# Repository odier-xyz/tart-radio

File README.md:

TART-Frontend
-------------

Radio module
------------

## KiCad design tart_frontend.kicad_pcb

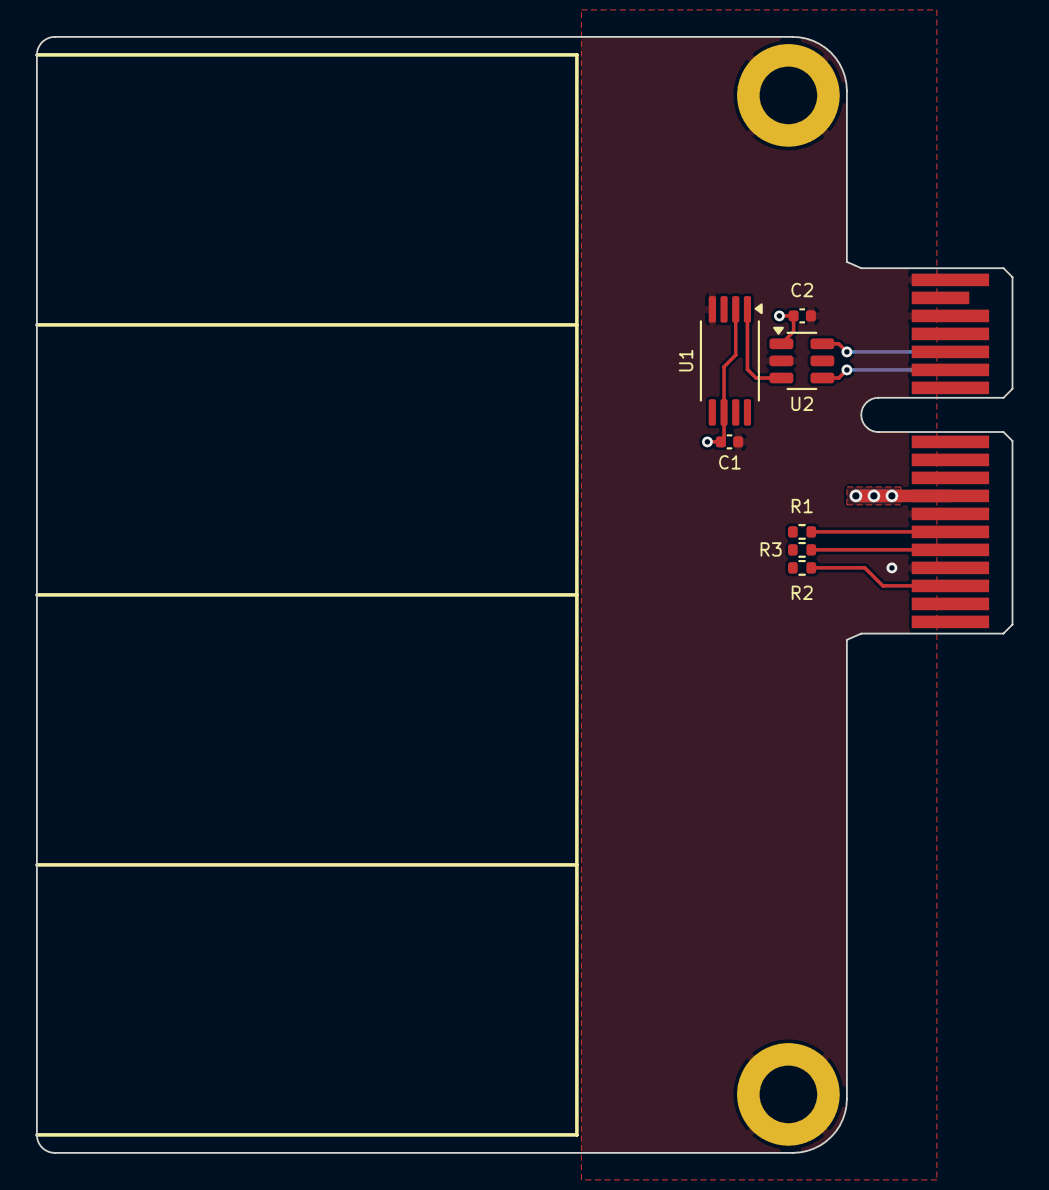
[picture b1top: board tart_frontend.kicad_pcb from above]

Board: 6 copper layers, 54.2 x 62.0 mm, 10 parts (0 on the bottom side), 8 nets.

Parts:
C1, C2: 100n; C_0402_1005Metric
H1, H2: GND; MountingHole_3.2mm_M3_ISO7380_Pad
J1: BUS_PCIexpress_x1
R1, R2, R3: 100; R_0402_1005Metric
U1: CDCV304PW; TSSOP-8_4.4x3mm_P0.65mm
U2: MAX3280E; SOT-23-6

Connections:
GNDREF: C1.1, C2.2, H1.1, H2.1, J1.A4 (GND), J1.A12 (GND), J1.A15 (GND), J1.A18 (GND), J1.B4 (GND), J1.B7 (GND), J1.B13 (GND), J1.B16 (GND), J1.B18 (GND), U1.4 (gnd), U2.2 (GND)
unnamed: J1.A13 (REFCLK+), U2.4 (B)
unnamed: J1.A14 (REFCLK-), U2.6 (A)
unnamed: J1.B6 (SCLK), R1.1
unnamed: J1.B3 (SDATA), R2.1
unnamed: J1.B5 (~CS), R3.1
unnamed: U1.1 (clkin), U2.3 (RO)
VCC: C1.2, C2.1, J1.A9 (+3.3V), J1.A10 (+3.3V), J1.B8 (+3.3V), U1.2 (oe), U1.6 (vdd), U2.1 (VCC)

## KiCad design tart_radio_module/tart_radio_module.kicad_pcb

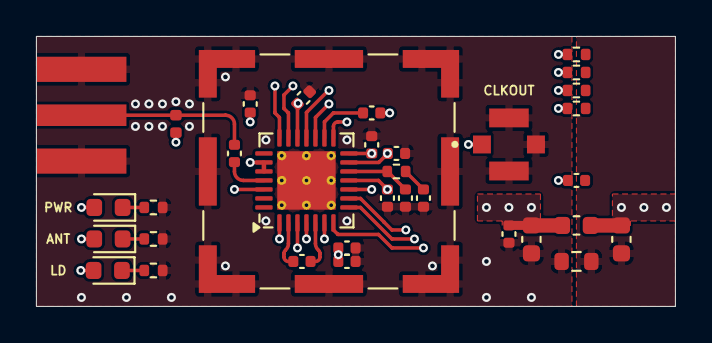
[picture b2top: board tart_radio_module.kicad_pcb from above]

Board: 6 copper layers, 35.5 x 15.0 mm, 34 parts (0 on the bottom side), 23 nets.

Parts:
C1, C9, C10, C12: 100nF; C_0402_1005Metric
C2: 27pF; C_0402_1005Metric
C3, C7, C8, C11, C15: 10nF; C_0402_1005Metric
C4, C16: 10uF; C_0603_1608Metric
C5: 47nF; C_0402_1005Metric
C6: 100pF; C_0402_1005Metric
C13, C14: 0.47nF; C_0402_1005Metric
D1, D2, D3: LED; D_0603_1608Metric
FB1: GZ1608D601TF; L_0603_1608Metric
J1: Conn_Coaxial; CONN-SMD_KH-SMA-KE8-G
J2: RFShield_OnePiece; Laird_Technologies_BMI-S-101_13.66x12.70mm
J3: Conn_Coaxial; CONN-SMD_MOLEX_73412-0110
L1: L; L_0402_1005Metric
R1, R2, R3: 1k; R_0402_1005Metric
R4: 20k; R_0402_1005Metric
R5, R6, R8, R9: 100; R_0402_1005Metric
R7: 1k; R_0603_1608Metric
U1: MAX2769B

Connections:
/+3V3_local: C1.1, C3.1, C4.1, C6.1, C7.2, C8.2, C9.1, C10.1, C12.1, D1.2 (A), FB1.2, U1.4 (VCC_RF), U1.11 (VCC_VCO), U1.13 (VCC_CP), U1.14 (VCCD), U1.19 (VCC_ADC), U1.23 (VCC_IF), U1.24 (IDLE#)
/AGND_local: C1.2, C2.2, C3.2, C4.2, C5.2, C6.2, C7.1, C8.1, C9.2, C10.2, C12.2, J1.2 (Ext), J2.1 (Shield), J3.2 (Ext), R1.2, R2.2, R3.2, R7.2, U1.29 (GND)
/ANT: D2.2 (A), U1.1 (ANTFLAG)
/I0: R6.1, U1.20 (I0)
/I1: R9.1, U1.21 (I1)
/LD: D3.2 (A), U1.6 (LD)
/Q0: R5.1, U1.18 (Q0)
/Q1: R8.1, U1.17 (Q1)
GNDREF: C16.2, R7.1
unnamed: C5.1, R4.1
unnamed: D1.1 (K), R3.1
unnamed: D2.1 (K), R2.1
unnamed: D3.1 (K), R1.1
unnamed: C13.1, J1.1 (In), L1.1
unnamed: C11.1, J3.1 (In)
unnamed: L1.2, U1.3 (ANTBIAS)
unnamed: C11.2, U1.16 (CLKOUT)
unnamed: C2.1, R4.2, U1.12 (CPOUT)
unnamed: C13.2, U1.25 (LNA2)
unnamed: C14.1, U1.2 (LNAOUT)
unnamed: C14.2, U1.5 (MIXIN)
unnamed: C15.2, U1.15 (XTAL)
VCC: C16.1, FB1.1
